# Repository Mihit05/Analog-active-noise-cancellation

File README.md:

# Analog Active Noise Cancellation System

## Overview
This project implements an analog active noise cancellation (ANC) system using op-amp based signal processing techniques. The goal is to reduce ambient noise through phase inversion and destructive interference.

## Key Features
- Fully analog design (no DSP)
- Phase inversion using all-pass filter
- Signal conditioning using op-amps
- Custom PCB design

## System Architecture

1. Noise input is captured via microphone
2. Signal is processed through:
   - Amplification stage
   - Phase inversion (all-pass filter)
3. Output signal is combined to cancel noise

## Circuit Design

- Op-Amps: LM741
- Key Blocks:
  - Amplifier
  - All-pass filter (phase shift)
  - Output driver

## PCB Layout

---

## Schematic

---

## Theory

Active Noise Cancellation works by generating a signal that is:
- Equal in amplitude
- Opposite in phase (180°)

When combined:
Noise + Anti-noise → Cancellation

## Challenges Faced

- Achieving precise phase shift
- Noise amplification instability
- Analog component tolerance issues

## Future Improvements

- Replace LM741 with low-noise op-amps
- Move to hybrid analog + DSP system
- Real-time adaptive filtering

## Author

Mihit Saxena

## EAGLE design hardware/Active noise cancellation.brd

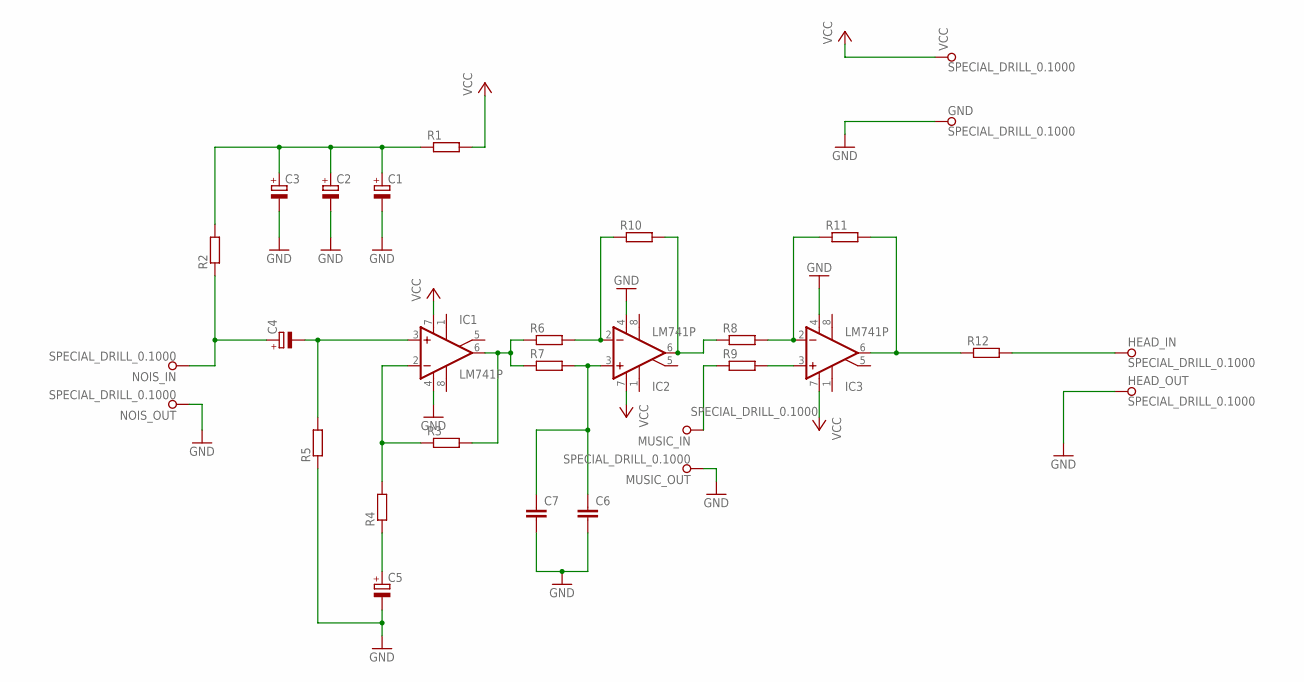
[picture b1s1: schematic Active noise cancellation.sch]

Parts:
C1, C2, C3, C4, C5: CPOL-EUE1.8-4; E1,8-4
C6, C7: C-EU050-024X044; C050-024X044
GND: SPECIAL_DRILL_0.1000; PAD_0.1000
HEAD_IN: SPECIAL_DRILL_0.1000; PAD_0.1000
HEAD_OUT: SPECIAL_DRILL_0.1000; PAD_0.1000
IC1, IC2, IC3: LM741P; DIL08
MUSIC_IN: SPECIAL_DRILL_0.1000; PAD_0.1000
MUSIC_OUT: SPECIAL_DRILL_0.1000; PAD_0.1000
NOIS_IN: SPECIAL_DRILL_0.1000; PAD_0.1000
NOIS_OUT: SPECIAL_DRILL_0.1000; PAD_0.1000
R1, R2, R3, R4, R5, R6, R7, R8, R9, R10, R11, R12: R-EU_0204/7; 0204/7
VCC: SPECIAL_DRILL_0.1000; PAD_0.1000

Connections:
GND: C1.-, C2.-, C3.-, C5.-, C6.2, C7.2, GND.1, HEAD_OUT.1, IC1.4 (V-), IC2.4 (V-), IC3.4 (V-), MUSIC_OUT.1, NOIS_OUT.1, R5.1
unnamed: C1.+, C2.+, C3.+, R1.1, R2.2
unnamed: IC2.6 (OUT), R8.1, R10.2
unnamed: C4.+, NOIS_IN.1, R2.1
unnamed: C4.-, IC1.3 (+IN), R5.2
unnamed: IC1.2 (-IN), R3.1, R4.2
unnamed: C5.+, R4.1
unnamed: IC1.6 (OUT), R3.2, R6.1, R7.1
unnamed: IC3.2 (-IN), R8.2, R11.1
unnamed: IC2.2 (-IN), R6.2, R10.1
unnamed: C6.1, C7.1, IC2.3 (+IN), R7.2
unnamed: IC3.6 (OUT), R11.2, R12.1
unnamed: MUSIC_IN.1, R9.1
unnamed: HEAD_IN.1, R12.2
unnamed: IC3.3 (+IN), R9.2
VCC: IC1.7 (V+), IC2.7 (V+), IC3.7 (V+), R1.2, VCC.1

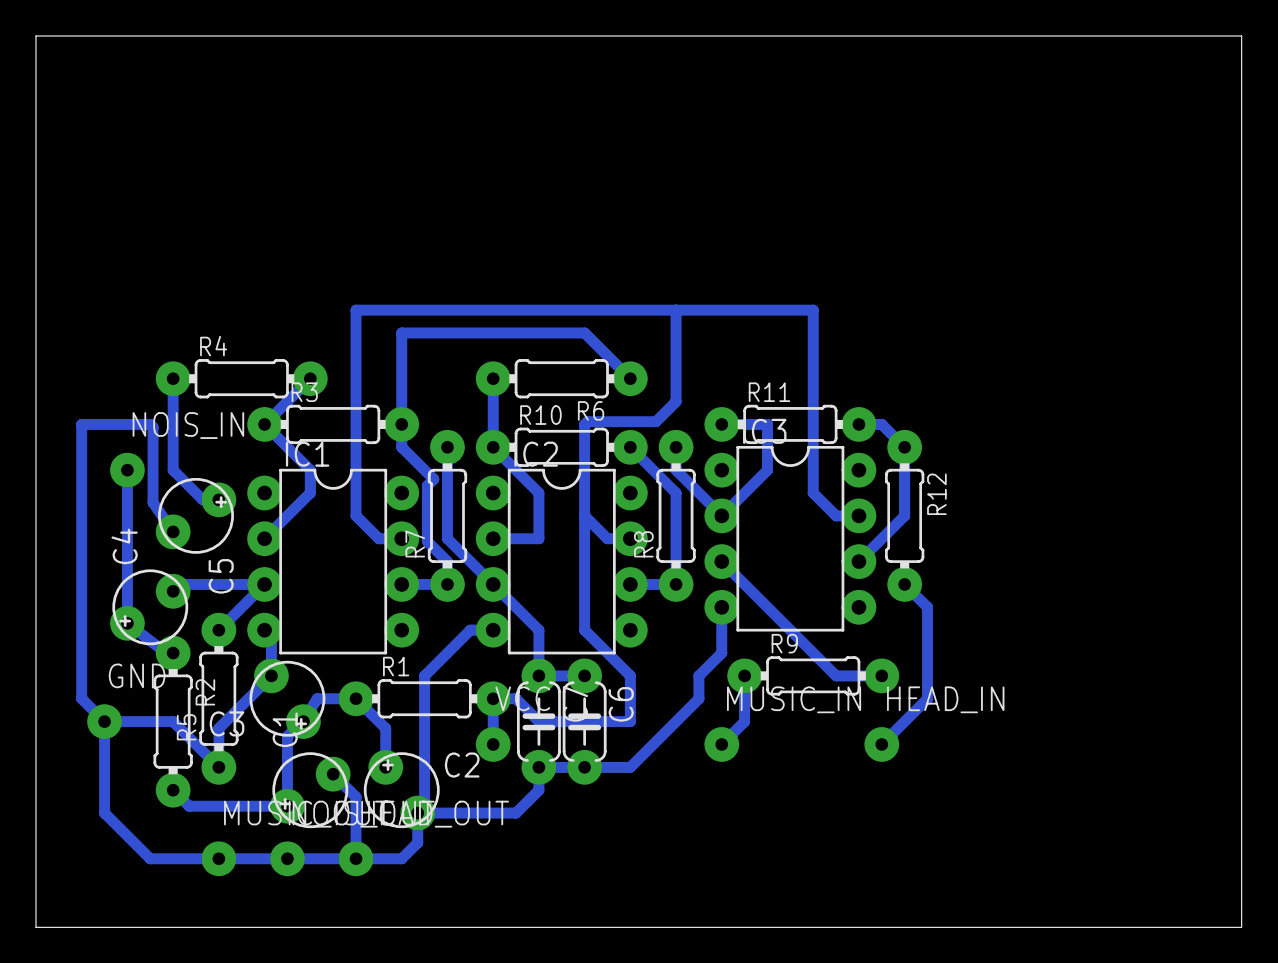
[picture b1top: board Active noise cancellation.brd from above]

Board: 2 copper layers, 67.0 x 49.5 mm, 30 parts (0 on the bottom side), 16 nets.

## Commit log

2026-04-05 Create hardware
2026-04-05 Create temp
2026-04-05 Rename Screenshot 2026-04-06 001512.png to pcb_layout.png
2026-04-05 Rename Screenshot 2026-04-06 001548.png to schematic.png
2026-04-05 Rename WhatsApp Video 2026-04-06 at 12.31.20 AM.mp4 to demo_vid.mp4
2026-04-05 Rename WhatsApp Image 2026-04-06 at 12.32.41 AM.jpeg to physical_pcb.jpeg
